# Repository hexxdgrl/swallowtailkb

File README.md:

Ergogen config and future keymaps for the swallowtail keyboard

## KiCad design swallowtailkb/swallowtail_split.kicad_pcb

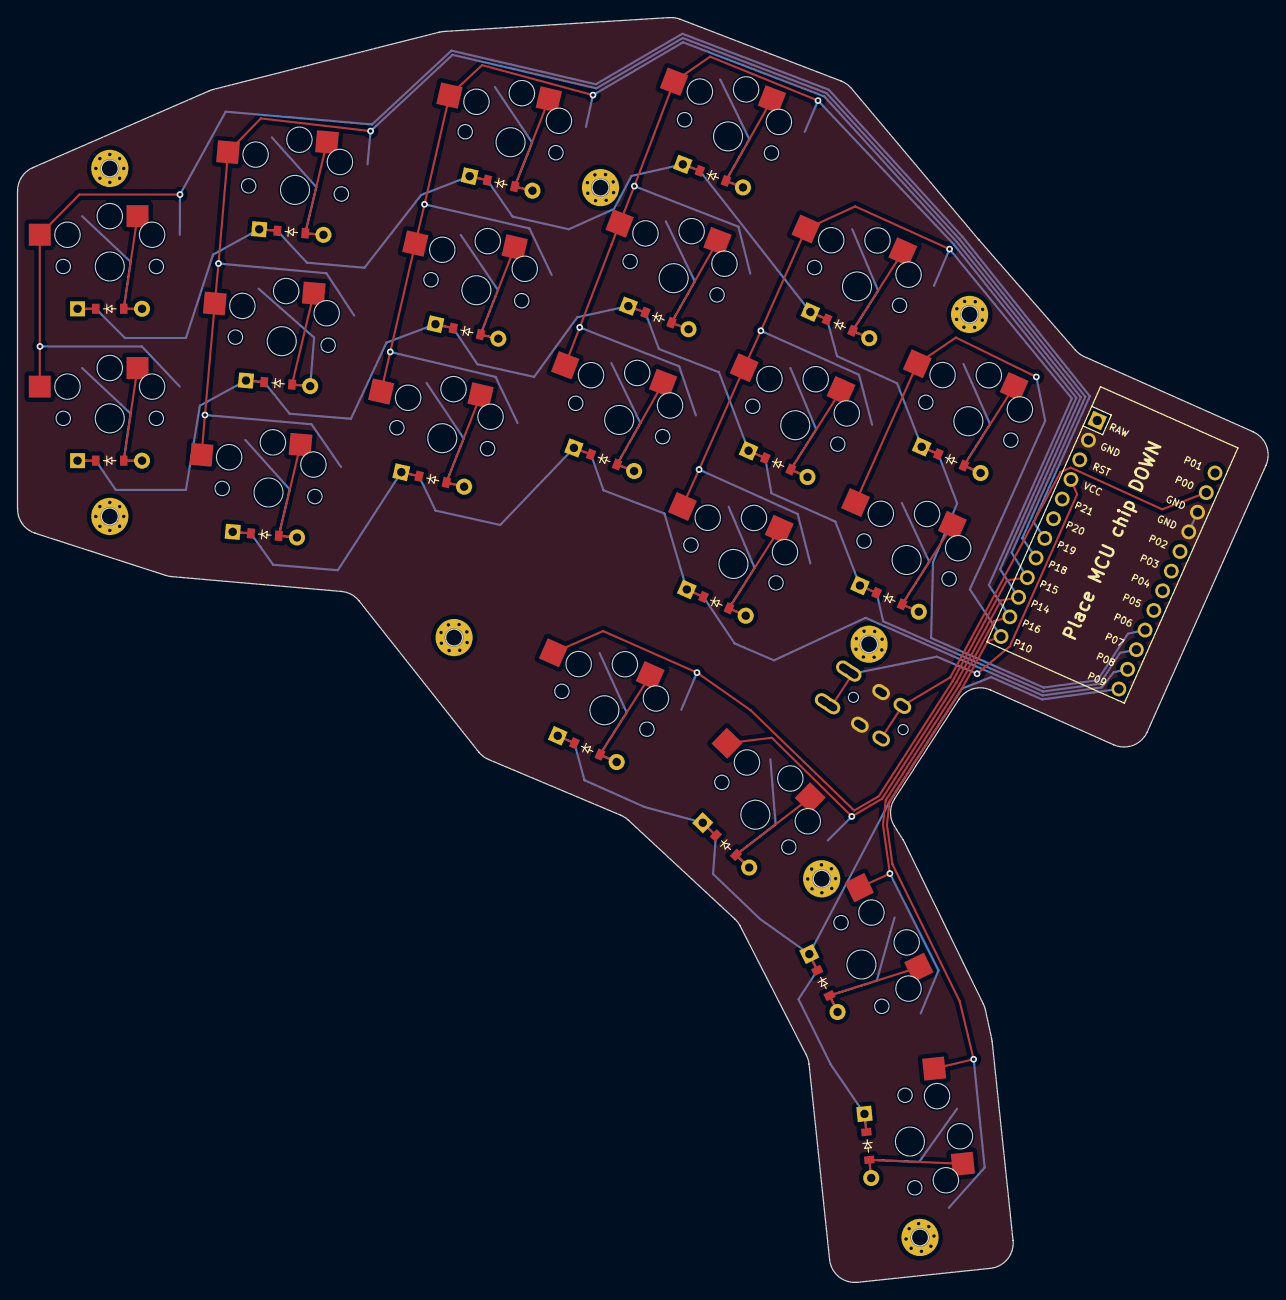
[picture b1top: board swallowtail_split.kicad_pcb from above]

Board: 2 copper layers, 147.8 x 149.5 mm, 50 parts (0 on the bottom side), 33 nets.

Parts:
D1, D2, D3, D4, D5, D6, D7, D8, D9, D10, D11, D12, D13, D14, D15, D16, D17, D18, D19, D20: ComboDiode
MCU1: ProMicro
S1, S2, S3, S4, S5, S6, S7, S8, S9, S10, S11, S12, S13, S14, S15, S16, S17, S18, S19, S20: PG1350
TRRS1: TRRS-PJ-320A-dual
_1, _2, _3, _4, _5, _6, _7, _8: MountingHole_2.2mm_M2_Pad_Via

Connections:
GND: MCU1.2, MCU1.15, MCU1.16, TRRS1.3
P0: MCU1.14, TRRS1.4
P6: D2.1, D5.1, D8.1, D11.1, D14.1, D16.1, MCU1.21
P7: D1.1, D4.1, D7.1, D10.1, D13.1, D15.1, MCU1.22
P8: D3.1, D6.1, D9.1, D12.1, MCU1.23
P9: D17.1, D18.1, D19.1, D20.1, MCU1.24
P10: MCU1.12, S15.2, S16.2, S20.2
P14: MCU1.10, S9.2, S10.2, S11.2, S18.2
P15: MCU1.9, S6.2, S7.2, S8.2, S17.2
P16: MCU1.11, S12.2, S13.2, S14.2, S19.2
P18: MCU1.8, S3.2, S4.2, S5.2
P19: MCU1.7, S1.2, S2.2
VCC: MCU1.4, TRRS1.2
far_thumb: D19.2, S19.1
farthest_thumb: D20.2, S20.1
home_thumb: D18.2, S18.1
index_bottom: D12.2, S12.1
index_home: D13.2, S13.1
index_top: D14.2, S14.1
inner_home: D15.2, S15.1
inner_top: D16.2, S16.1
middle_bottom: D9.2, S9.1
middle_home: D10.2, S10.1
middle_top: D11.2, S11.1
near_thumb: D17.2, S17.1
outer_home: D1.2, S1.1
outer_top: D2.2, S2.1
pinky_bottom: D3.2, S3.1
pinky_home: D4.2, S4.1
pinky_top: D5.2, S5.1
ring_bottom: D6.2, S6.1
ring_home: D7.2, S7.1
ring_top: D8.2, S8.1

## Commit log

2024-08-30 init
2024-08-30 readme
2024-08-31 Added split config (indev)
2024-09-03 added individual configs for split and non split versions, kicad dir and files, wip PCB for split kb
2024-10-10 added case conf
